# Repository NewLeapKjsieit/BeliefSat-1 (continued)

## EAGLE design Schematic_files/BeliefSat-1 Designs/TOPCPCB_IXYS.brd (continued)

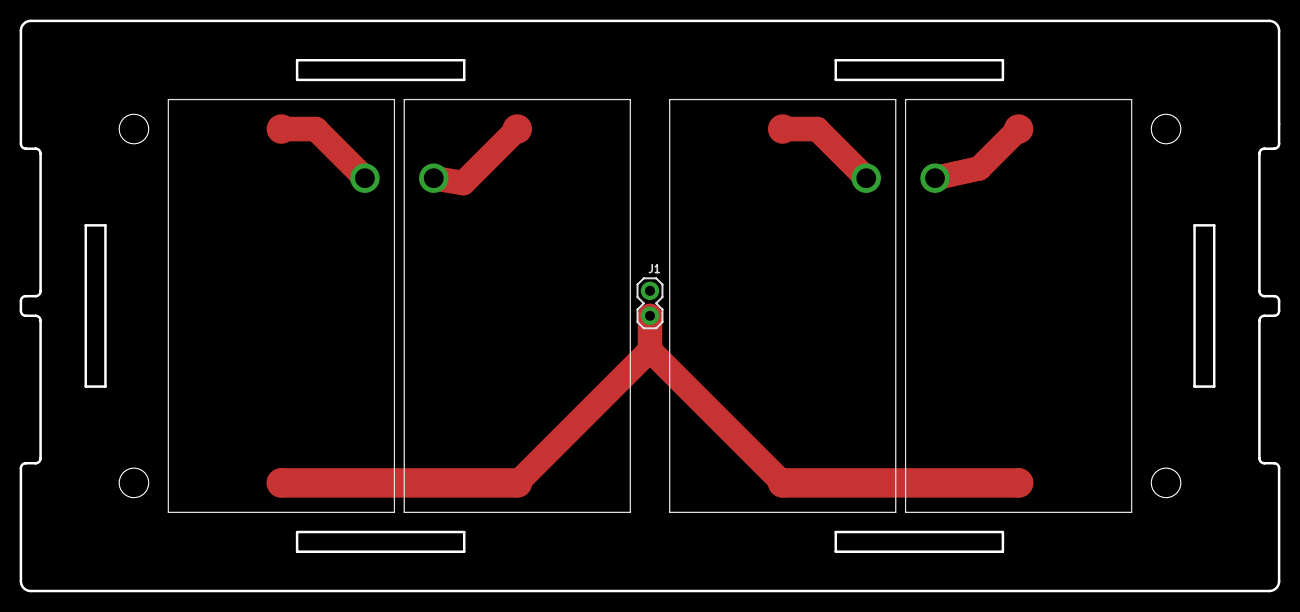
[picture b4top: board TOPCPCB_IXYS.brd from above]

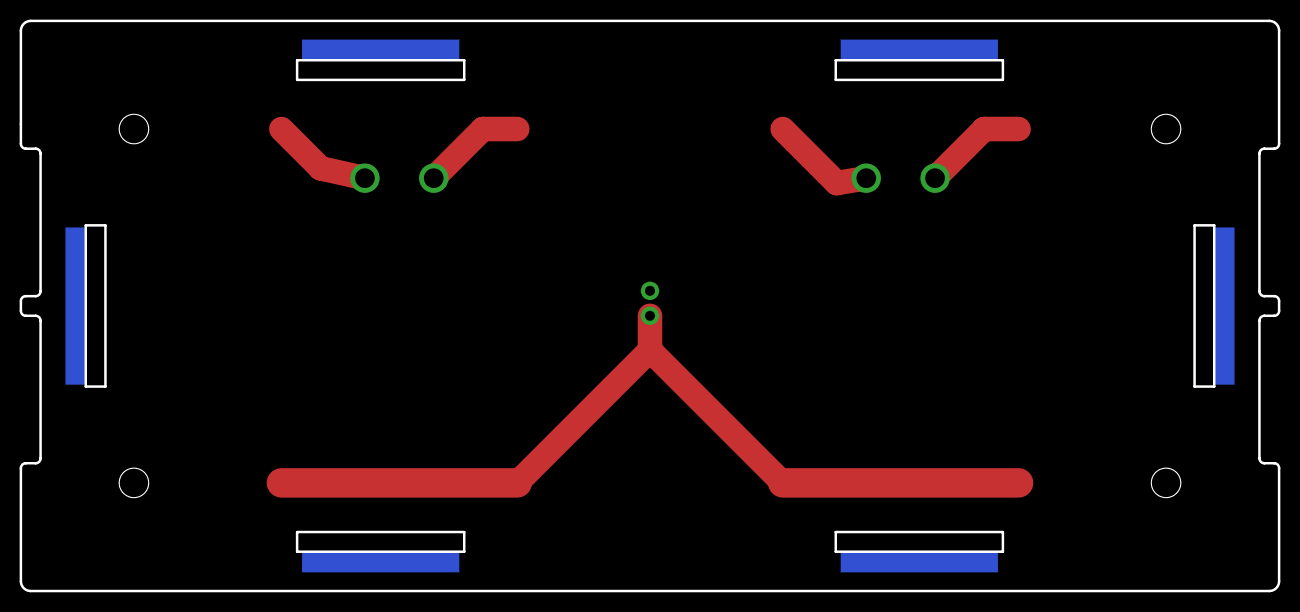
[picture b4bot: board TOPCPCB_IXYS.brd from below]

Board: 2 copper layers, 128.0 x 58.0 mm, 11 parts (6 on the bottom side), 2 nets.

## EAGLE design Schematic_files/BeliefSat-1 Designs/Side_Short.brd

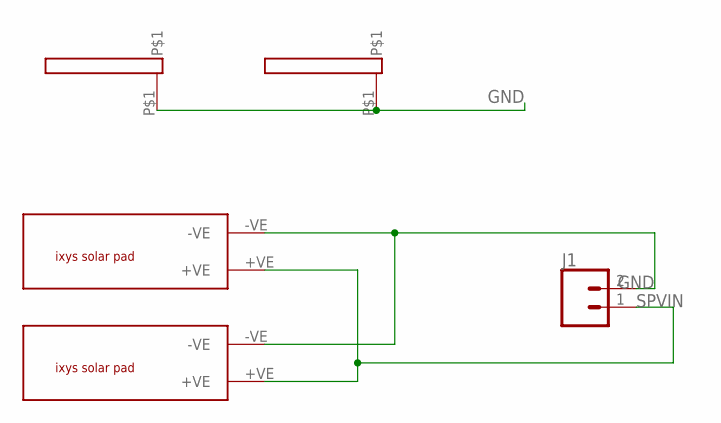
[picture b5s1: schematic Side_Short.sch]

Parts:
J1: CONN_02; 1X02
U$1, U$2: IXYS
U$3, U$4: 16X2

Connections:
GND: J1.2, U$1.-VE, U$2.-VE, U$3.P$1, U$4.P$1
SPVIN: J1.1, U$1.+VE, U$2.+VE

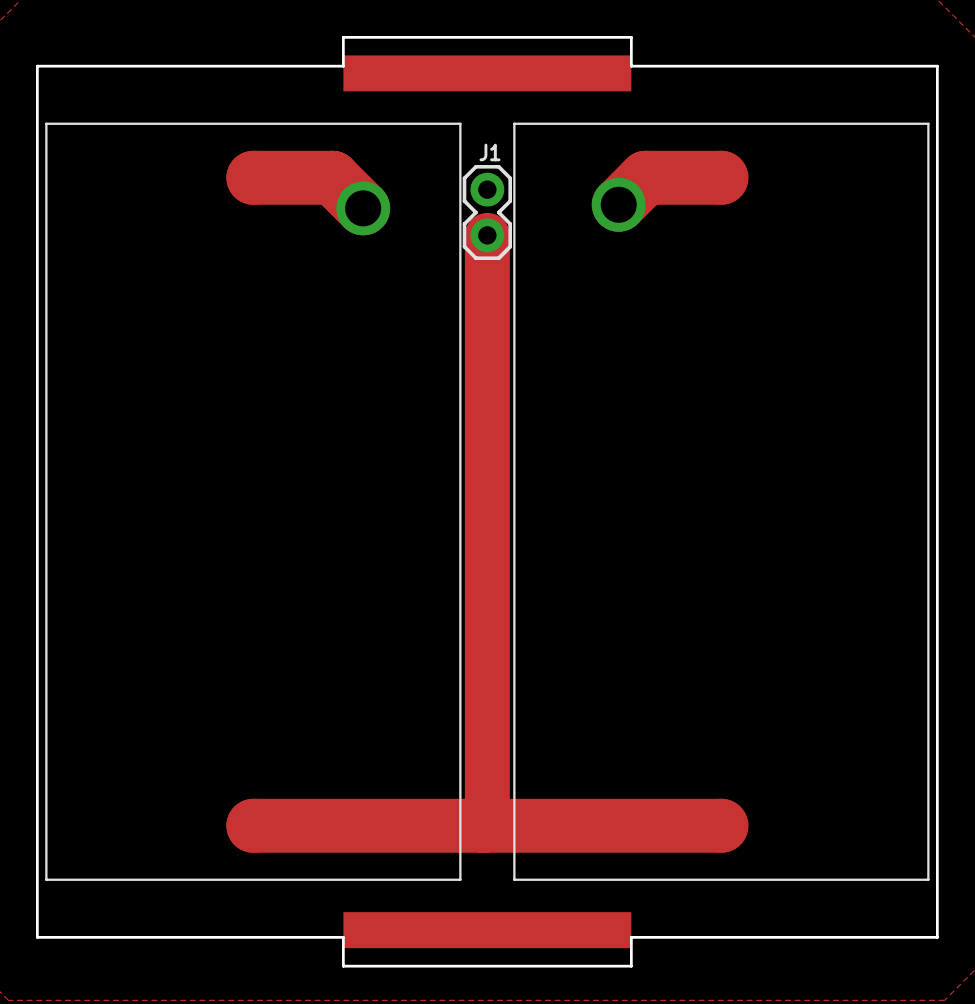
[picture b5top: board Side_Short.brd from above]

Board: 2 copper layers, 50.0 x 51.6 mm, 5 parts (0 on the bottom side), 2 nets.

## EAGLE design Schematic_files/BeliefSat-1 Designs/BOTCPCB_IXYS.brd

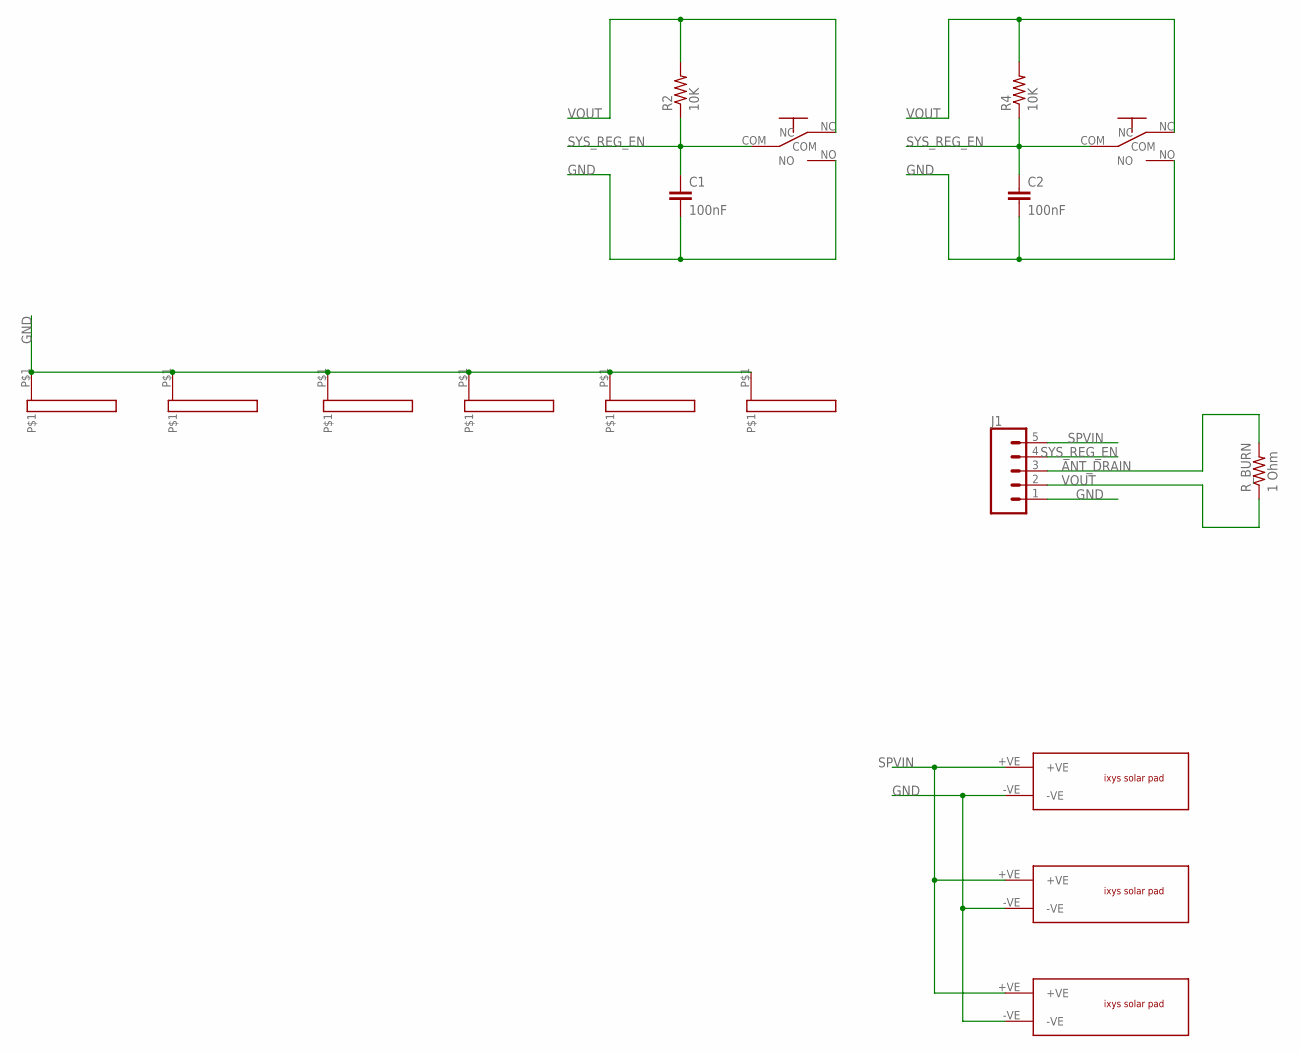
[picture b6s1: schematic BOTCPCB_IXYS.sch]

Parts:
C1, C2: 100nF; C025-024X044
J1: CONN_05NO_SILK; 1X05_NO_SILK
R2, R4: 10K; 0204/5
R_BURN: 1 Ohm; 0204/5
U$1, U$2, U$4, U$5, U$7, U$8: 16X2
U$3, U$6: OMRON-D2FA; OMRON-D2F-A
U$9, U$11, U$12: IXYS

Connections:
ANT_DRAIN: J1.3, R_BURN.2
GND: C1.2, C2.2, J1.1, U$1.P$1, U$2.P$1, U$3.NO, U$4.P$1, U$5.P$1, U$6.NO, U$7.P$1, U$8.P$1, U$9.-VE, U$11.-VE, U$12.-VE
SPVIN: J1.5, U$9.+VE, U$11.+VE, U$12.+VE
SYS_REG_EN: C1.1, C2.1, J1.4, R2.1, R4.1, U$3.COM, U$6.COM
VOUT: J1.2, R2.2, R4.2, R_BURN.1, U$3.NC, U$6.NC

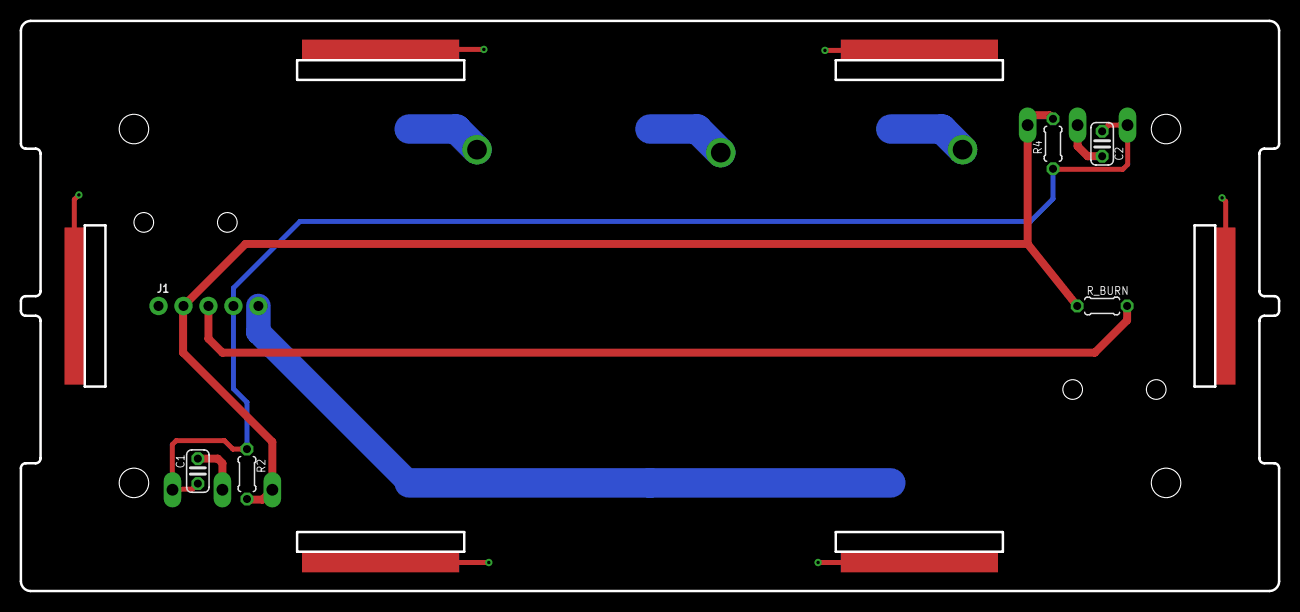
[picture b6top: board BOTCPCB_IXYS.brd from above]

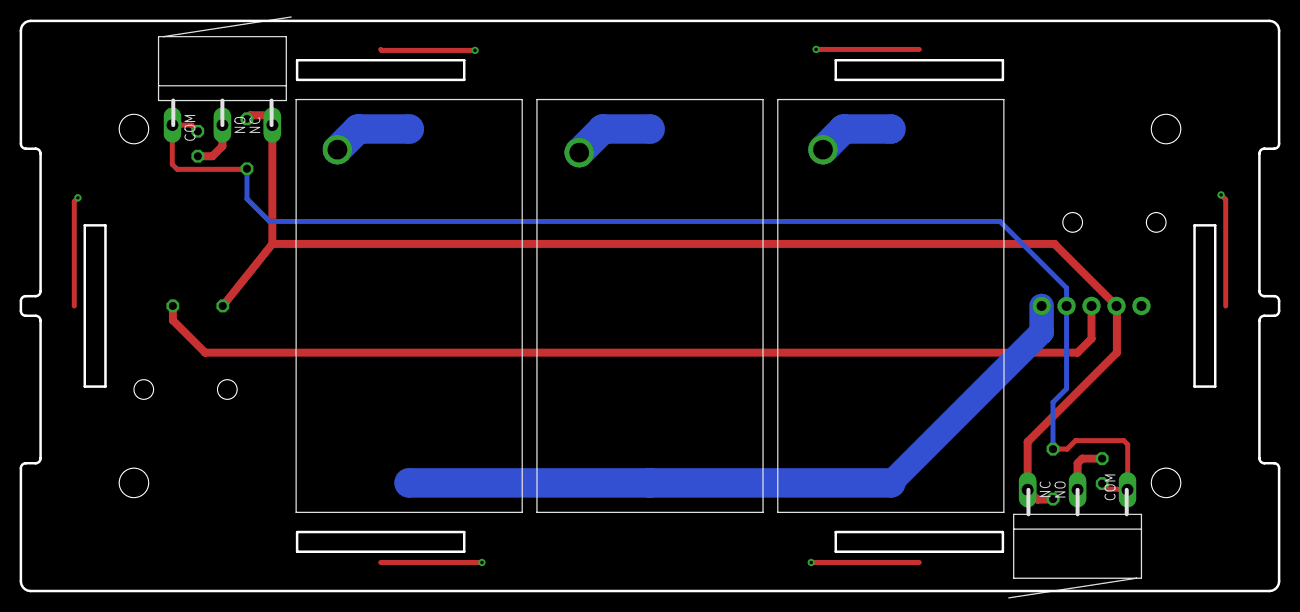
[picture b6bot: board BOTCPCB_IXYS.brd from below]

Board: 2 copper layers, 128.0 x 58.0 mm, 17 parts (5 on the bottom side), 5 nets.

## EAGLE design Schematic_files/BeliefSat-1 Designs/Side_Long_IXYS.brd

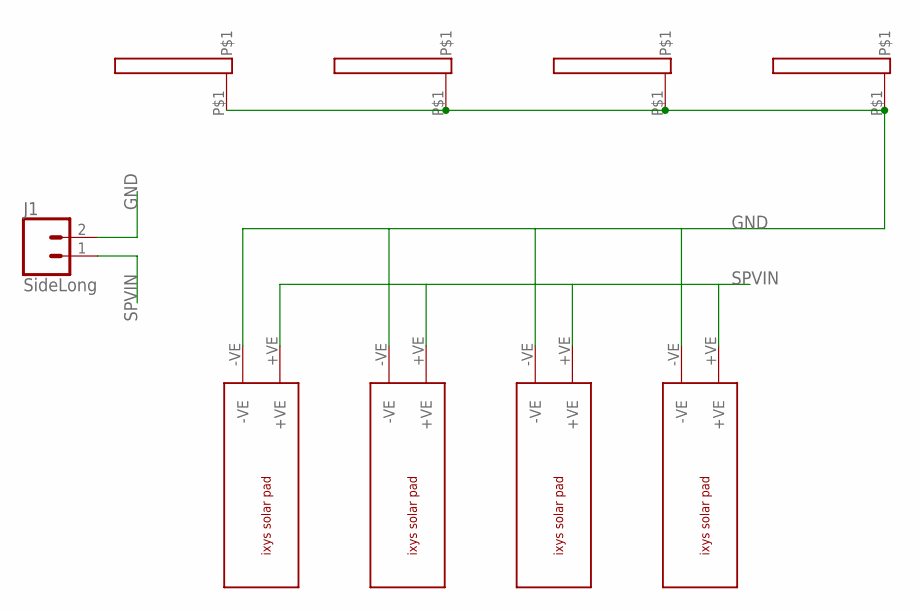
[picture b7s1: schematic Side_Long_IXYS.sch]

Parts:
J1: SideLong; 1X02
U$1, U$2, U$3, U$4: 16X2
U$9, U$10, U$11, U$12: IXYS

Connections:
GND: J1.2, U$1.P$1, U$2.P$1, U$3.P$1, U$4.P$1, U$9.-VE, U$10.-VE, U$11.-VE, U$12.-VE
SPVIN: J1.1, U$9.+VE, U$10.+VE, U$11.+VE, U$12.+VE

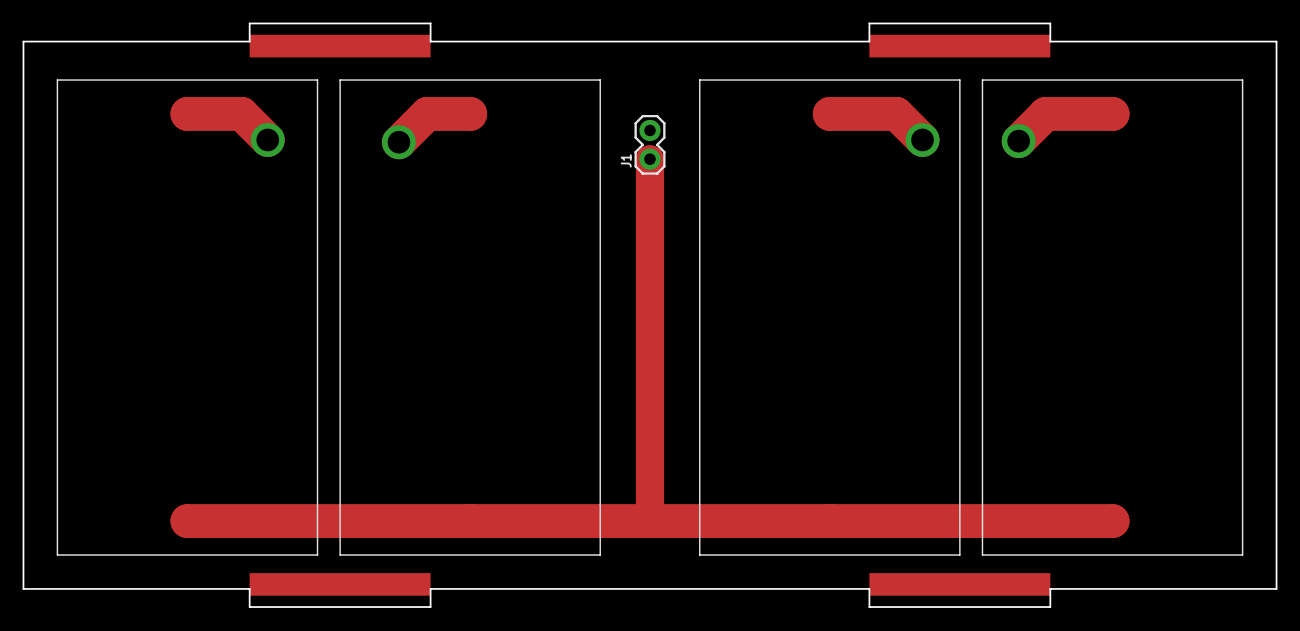
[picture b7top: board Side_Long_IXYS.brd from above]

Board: 2 copper layers, 110.8 x 51.6 mm, 9 parts (0 on the bottom side), 2 nets.

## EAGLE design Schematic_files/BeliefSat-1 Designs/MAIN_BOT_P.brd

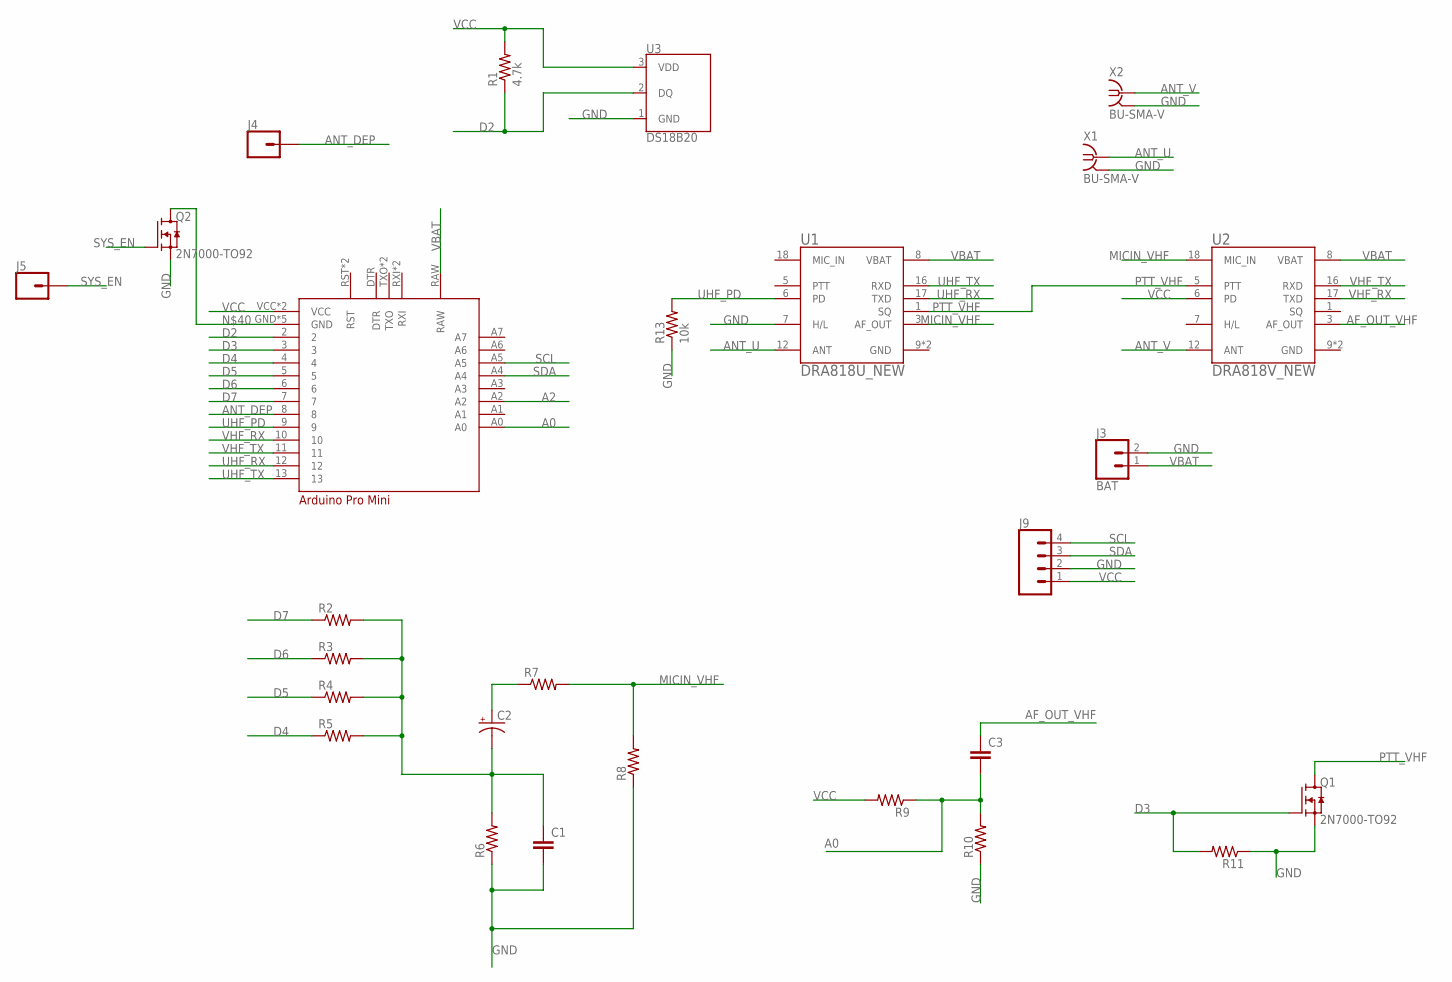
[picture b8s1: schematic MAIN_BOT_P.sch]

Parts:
C1, C3: C-EU025-024X044; C025-024X044
C2: CPOL-USE1.8-4; E1,8-4
J3: BAT; 1X02
J4, J5: CONN_01; 1X01
J9: CONN_04PTH; 1X04
Q1, Q2: 2N7000-TO92; TO92
R1: 4.7k; 0204/5
R2, R3, R4, R5, R6, R7, R8, R9, R10, R11: R-US_0204/5; 0204/5
R13: 10k; 0204/5
U1: DRA818U_NEW; DORJI_DRA818U_NEW
U2: DRA818V_NEW; DORJI_DRA818V_NEW
U3: DS18B20; TO-92-AMMO
U$1: ARDUNIO_PRO_MINI; ARDUINOPROMINI
X1, X2: BU-SMA-V

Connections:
A0: C3.2, R9.1, R10.2, U$1.A0
A2: U$1.A2
AF_OUT_VHF: C3.1, U2.3 (AF_OUT)
ANT_DEP: J4.1, U$1.8
ANT_U: U1.12 (ANT), X1.1
ANT_V: U2.12 (ANT), X2.1
D2: R1.1, U3.2 (DQ), U$1.2
D3: Q1.2 (G), R11.2, U$1.3
D4: R5.1, U$1.4
D5: R4.1, U$1.5
D6: R3.1, U$1.6
D7: R2.1, U$1.7
GND: C1.2, J3.2, J9.2, Q1.3 (S), Q2.3 (S), R6.1, R8.1, R10.1, R11.1, R13.1, U1.7 (H/L), U1.9 (GND), U1.10 (GND), U2.9 (GND), U2.10 (GND), U3.1 (GND), X1.2, X1.3 (2), X1.4 (2), X1.5 (2), X2.2, X2.3 (2), X2.4 (2), X2.5 (2)
MICIN_VHF: R7.2, R8.2, U1.3 (AF_OUT), U2.18 (MIC_IN)
unnamed: C2.+, R7.1
unnamed: C1.1, C2.-, R2.2, R3.2, R4.2, R5.2, R6.2
unnamed: Q2.1 (D), U$1.GND, U$1.GND2 (GND), U$1.GND3 (GND), U$1.GND4 (GND), U$1.GND5 (GND)
PTT_VHF: Q1.1 (D), U1.1 (SQ), U2.5 (PTT)
SCL: J9.4, U$1.A5
SDA: J9.3, U$1.A4
SYS_EN: J5.1, Q2.2 (G)
UHF_PD: R13.2, U1.6 (PD), U$1.9
UHF_RX: U1.17 (TXD), U$1.12
UHF_TX: U1.16 (RXD), U$1.13
VBAT: J3.1, U1.8 (VBAT), U2.8 (VBAT), U$1.RAW
VCC: J9.1, R1.2, R9.2, U2.6 (PD), U3.3 (VDD), U$1.VCC, U$1.VCC1 (VCC)
VHF_RX: U2.17 (TXD), U$1.10
VHF_TX: U2.16 (RXD), U$1.11

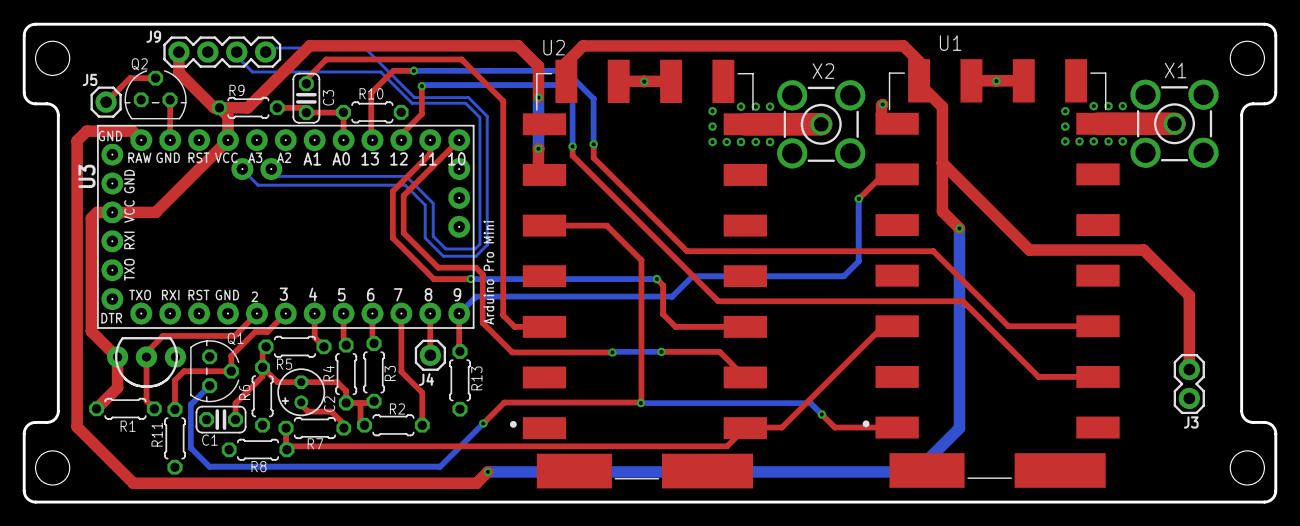
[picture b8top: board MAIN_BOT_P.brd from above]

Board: 2 copper layers, 110.0 x 42.0 mm, 27 parts (0 on the bottom side), 27 nets.

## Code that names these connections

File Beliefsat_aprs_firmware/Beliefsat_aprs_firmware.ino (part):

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
#define ANTENNA_DEPLOYMENT_PIN (8)
#define UHF_POWER_DOWN_PIN (9)
#define UHF_RX (12)
#define UHF_TX (13)
#define VHF_RX (10)
#define VHF_TX (11)
#define TEMPERATURE_SENSOR_PIN 2

String temp_sensor_1 = "";
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
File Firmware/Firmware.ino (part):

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#define north_enable_pin 18

// ANCHOR LORA
#define LORA_BUSY 4
#define LORA_DIO1 10
#define LORA_NRST 0
#define LORA_NSS 3
#define LORA_DIO3 1

// ANCHOR Camera Macros
#define Camera_enable_pin 12
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
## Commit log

2020-05-09 Edited readme
2020-05-11 added firmware psuedo packet generator
2020-05-11 Update test-compile.yml
    Added Arduino:avr to the build step to that avr g++ file exists
2020-05-11 Update test-compile.yml
    Changed the build prlatform to ubuntu to save time and resources
2020-05-12 documents
2020-05-29 Schematic files for the design created for proposal for PS4 Orbital Platform
2020-05-29 SIde plates, top and bottom plates for the design
2020-06-30 Recordings on SDRSharp
2020-06-30 moved recodings
2020-07-02 pseudo packet generator
2020-07-02 Rename sketch_jun20a.ino to packetGen.ino
2020-07-06 Update ssdvpacket.ino
    Setendcoding added
2020-07-06 Update ssdvpacket.ino
    Syntax Changes of packets
    Added 0x
2020-07-06 SSDV IQ AF reacordings on SDRSharp
2020-07-24 Update README.md
    Changed the sensor data format in the light of additional solar cells
2020-12-01 Adding Light sensor code with header file
2020-12-01 Create gyrosensor.ino
    Code for gyrosensor MPU6050
2021-01-24 Fixed Errors
2021-01-24 Fixed errors in imports and function call.
    Updated the annoying code indentation.
2021-01-24 Update void loop
2021-01-24 added .gitignorre
2021-01-27 Updated .gitignore to stop uploading .vscode
2021-01-31 Fixed a few errors in Firmware.ino
2021-02-10 Issue with macros
2021-02-10 Fixed issue with macros
2021-02-22 Reset counts in persistent SRAM
2021-02-24 Testing
2021-02-24 Testing INA219
2021-04-16 BeliefSat-1
2021-04-16 Serendipity
